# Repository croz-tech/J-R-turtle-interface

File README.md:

# J-R-turtle-interface
Re-creation of the Jessop-Ralph turtle interface for the BBC Micro range of home computers.

Connects to the BBC Micro user port (20 way IDC) and the turtle via a 15 way D connector.
Requires a +5V stabilised power supply which can be taken from the BBC Micro's aux power output.  However this is often used for disk drives, therefore a seperate power supply can be used.  Interface and turtle are comatible with Acornsoft Logo (using the JESSOP) extension.  It can also be used with DART software or driven directly via user port commands.

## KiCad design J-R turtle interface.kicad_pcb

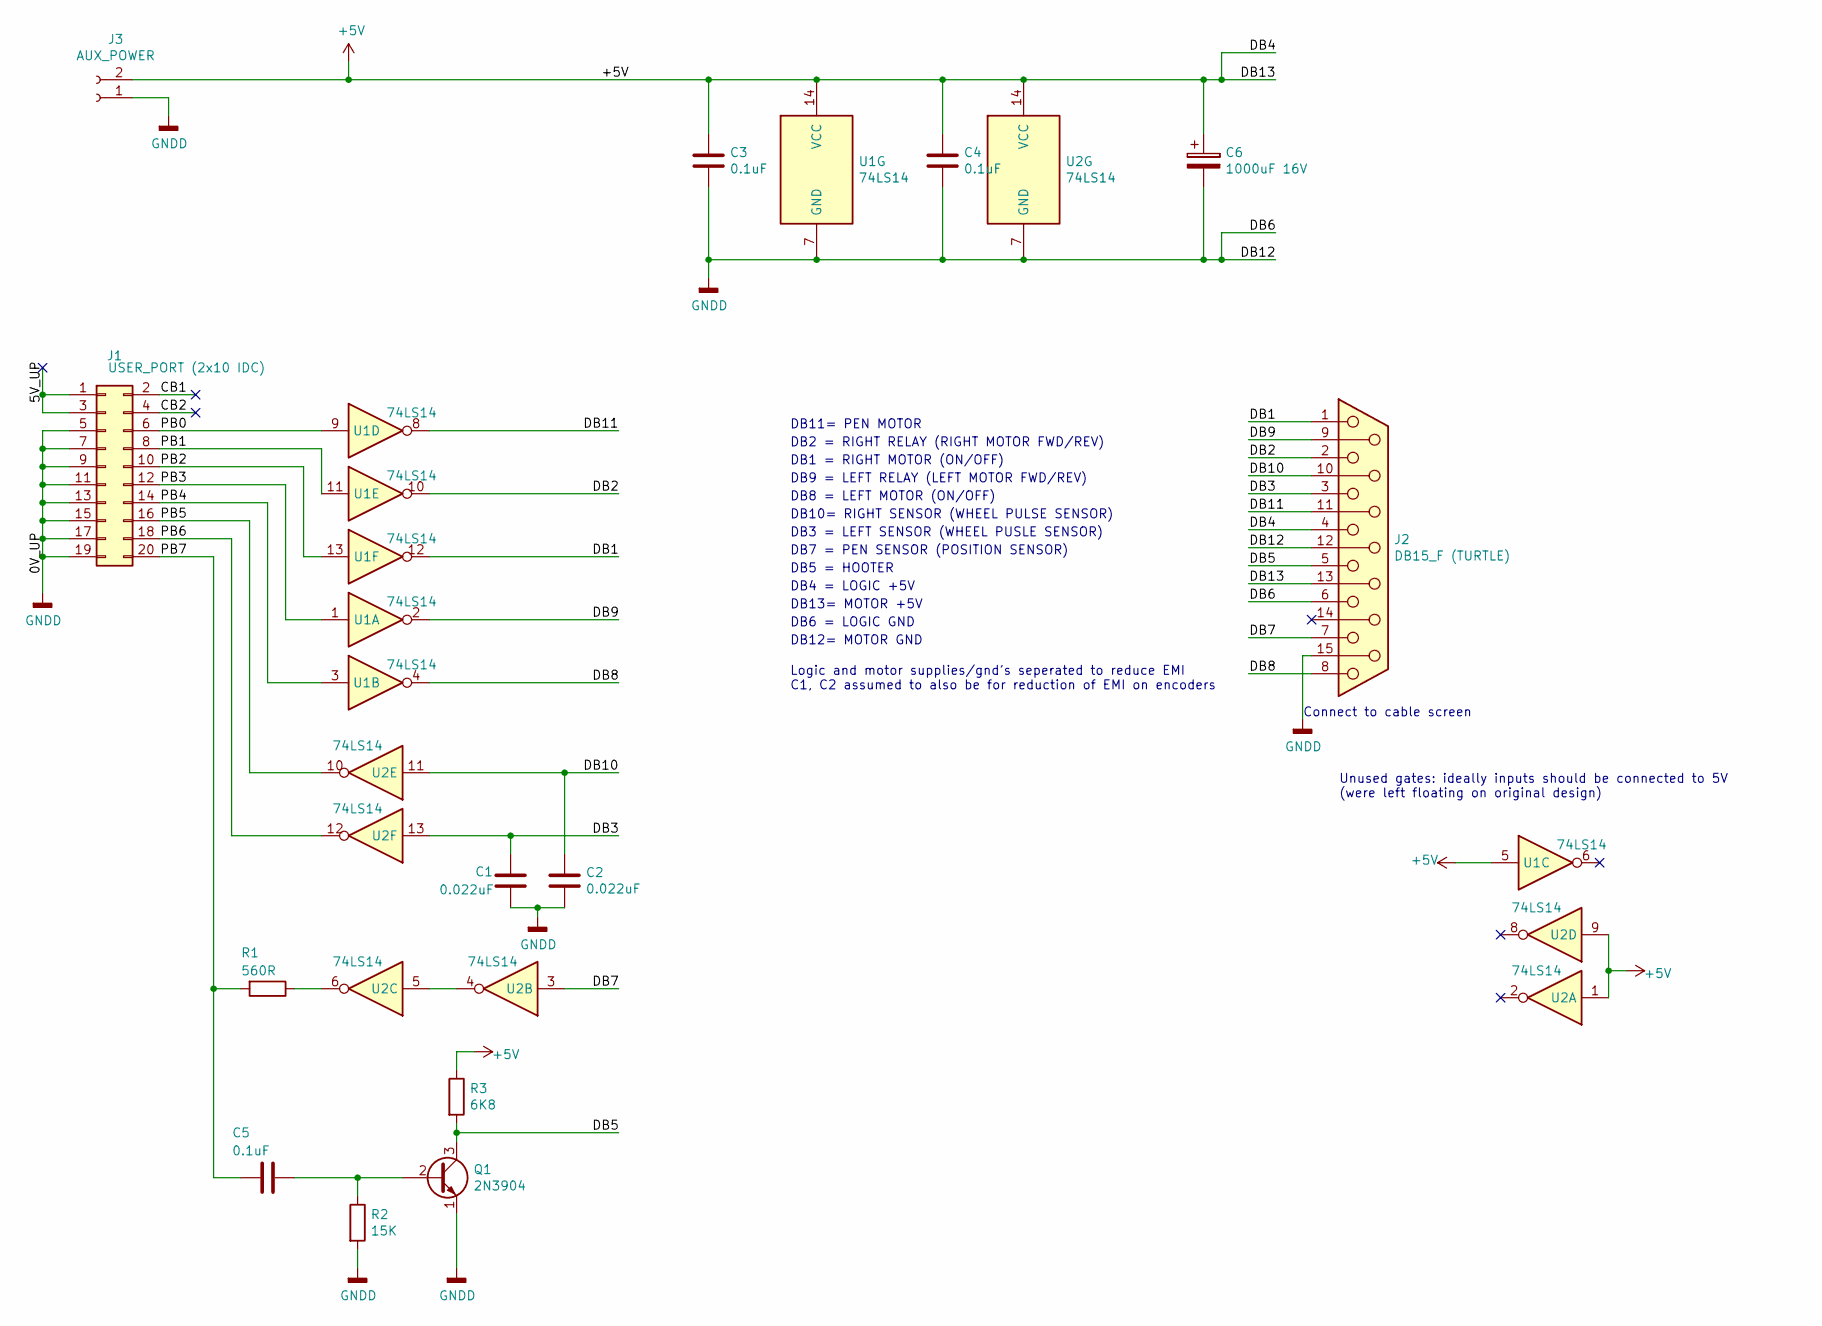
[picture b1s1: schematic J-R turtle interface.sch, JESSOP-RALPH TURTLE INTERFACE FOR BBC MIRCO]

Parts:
C1, C2: 0.022uF; C_Rect_L7.2mm_W2.5mm_P5.00mm_FKS2_FKP2_MKS2_MKP2
C3, C4, C5: 0.1uF; C_Rect_L7.2mm_W2.5mm_P5.00mm_FKS2_FKP2_MKS2_MKP2
C6: 1000uF 16V; CP_Radial_D10.0mm_P5.00mm
J1: USER_PORT (2x10 IDC); 20W_IDC_TERM
J2: DB15_F (TURTLE); PinHeader_1x15_P2.54mm_Vertical
J3: AUX_POWER; PinHeader_1x02_P2.54mm_Vertical
Q1: 2N3904; TO-92_Inline
R1: 560R; R_Axial_DIN0207_L6.3mm_D2.5mm_P10.16mm_Horizontal
R2: 15K; R_Axial_DIN0207_L6.3mm_D2.5mm_P10.16mm_Horizontal
R3: 6K8; R_Axial_DIN0207_L6.3mm_D2.5mm_P10.16mm_Horizontal
U1, U2: 74LS14; DIP-14_W7.62mm

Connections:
+5V: C3.1, C4.1, C6.1, J2.4, J2.13, J3.2, R3.1, U1.5, U1.14 (VCC), U2.1, U2.9, U2.14 (VCC)
/5V_UP: J1.1, J1.3
/CB1: J1.2
/CB2: J1.4
/DB1: J2.1, U1.12
/DB2: J2.2, U1.10
/DB3: C1.1, J2.3, U2.13
/DB5: J2.5, Q1.3 (C), R3.2
/DB7: J2.7, U2.3
/DB8: J2.8, U1.4
/DB9: J2.9, U1.2
/DB10: C2.1, J2.10, U2.11
/DB11: J2.11 (P111), U1.8
/PB0: J1.6, U1.9
/PB1: J1.8, U1.11
/PB2: J1.10, U1.13
/PB3: J1.12, U1.1
/PB4: J1.14, U1.3
/PB5: J1.16, U2.10
/PB6: J1.18, U2.12
/PB7: C5.2, J1.20, R1.2
GNDD: C1.2, C2.2, C3.2, C4.2, C6.2, J1.5, J1.7, J1.9, J1.11, J1.13, J1.15, J1.17, J1.19, J2.6, J2.12, J2.15, J3.1, Q1.1 (E), R2.2, U1.7 (GND), U2.7 (GND)
unnamed: C5.1, Q1.2 (B), R2.1
unnamed: R1.1, U2.6
unnamed: U2.4, U2.5

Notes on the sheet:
Unused gates: ideally inputs should be connected to 5V (were left floating on original design)
DB11= PEN MOTOR
DB2 = RIGHT RELAY (RIGHT MOTOR FWD/REV)
DB1 = RIGHT MOTOR (ON/OFF)
DB9 = LEFT RELAY (LEFT MOTOR FWD/REV)
DB8 = LEFT MOTOR (ON/OFF)
DB10= RIGHT SENSOR (WHEEL PULSE SENSOR)
DB3 = LEFT SENSOR (WHEEL PUSLE SENSOR)
DB7 = PEN SENSOR (POSITION SENSOR)
DB5 = HOOTER
DB4 = LOGIC +5V
DB13= MOTOR +5V
DB6 = LOGIC GND
DB12= MOTOR GND
Logic and motor supplies/gnd’s seperated to reduce EMI C1, C2 assumed to also be for reduction of EMI on encoders
Connect to cable screen

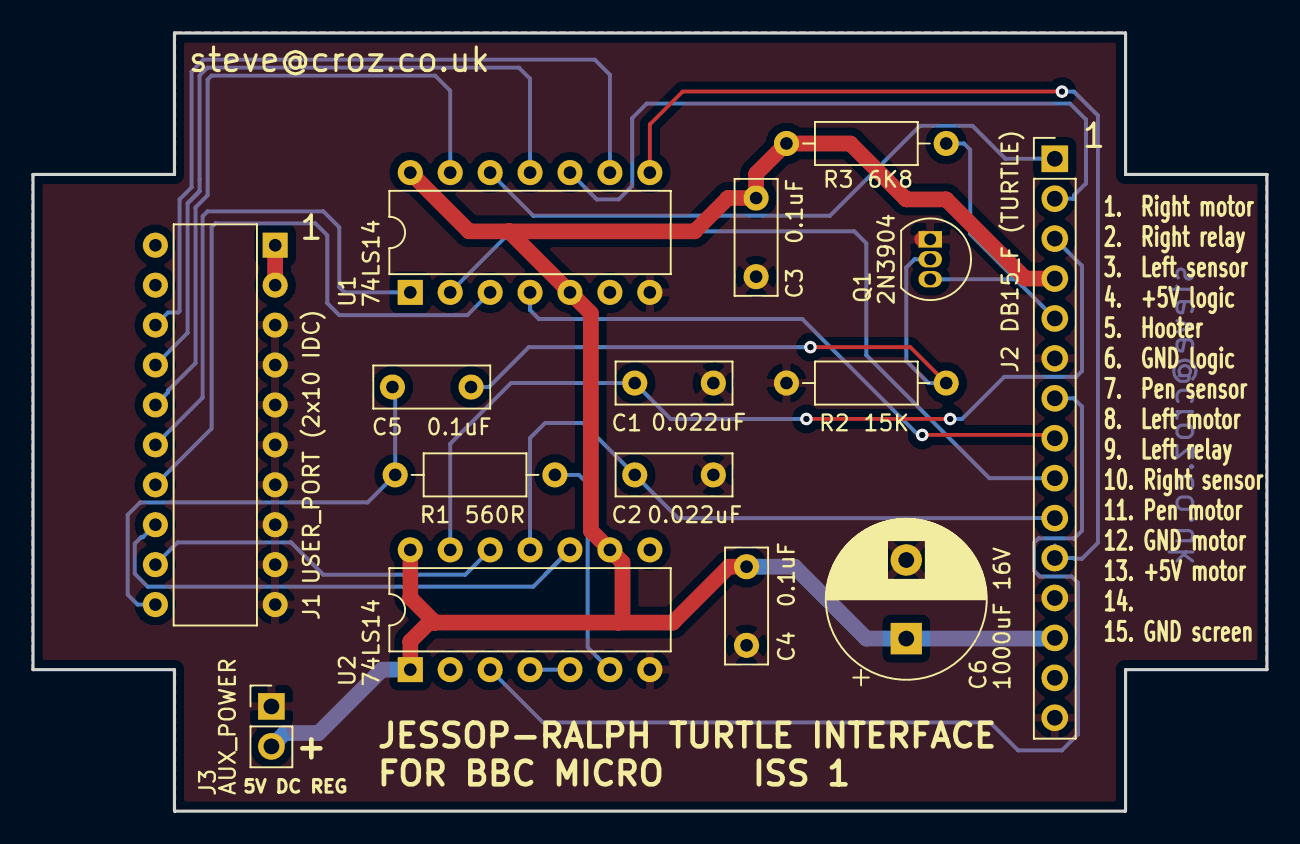
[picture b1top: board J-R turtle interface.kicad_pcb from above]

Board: 2 copper layers, 78.5 x 49.5 mm, 15 parts (0 on the bottom side), 23 nets.
